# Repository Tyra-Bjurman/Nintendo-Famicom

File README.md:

# Nintendo Famicom
 Educational Nintendo Famicom Project

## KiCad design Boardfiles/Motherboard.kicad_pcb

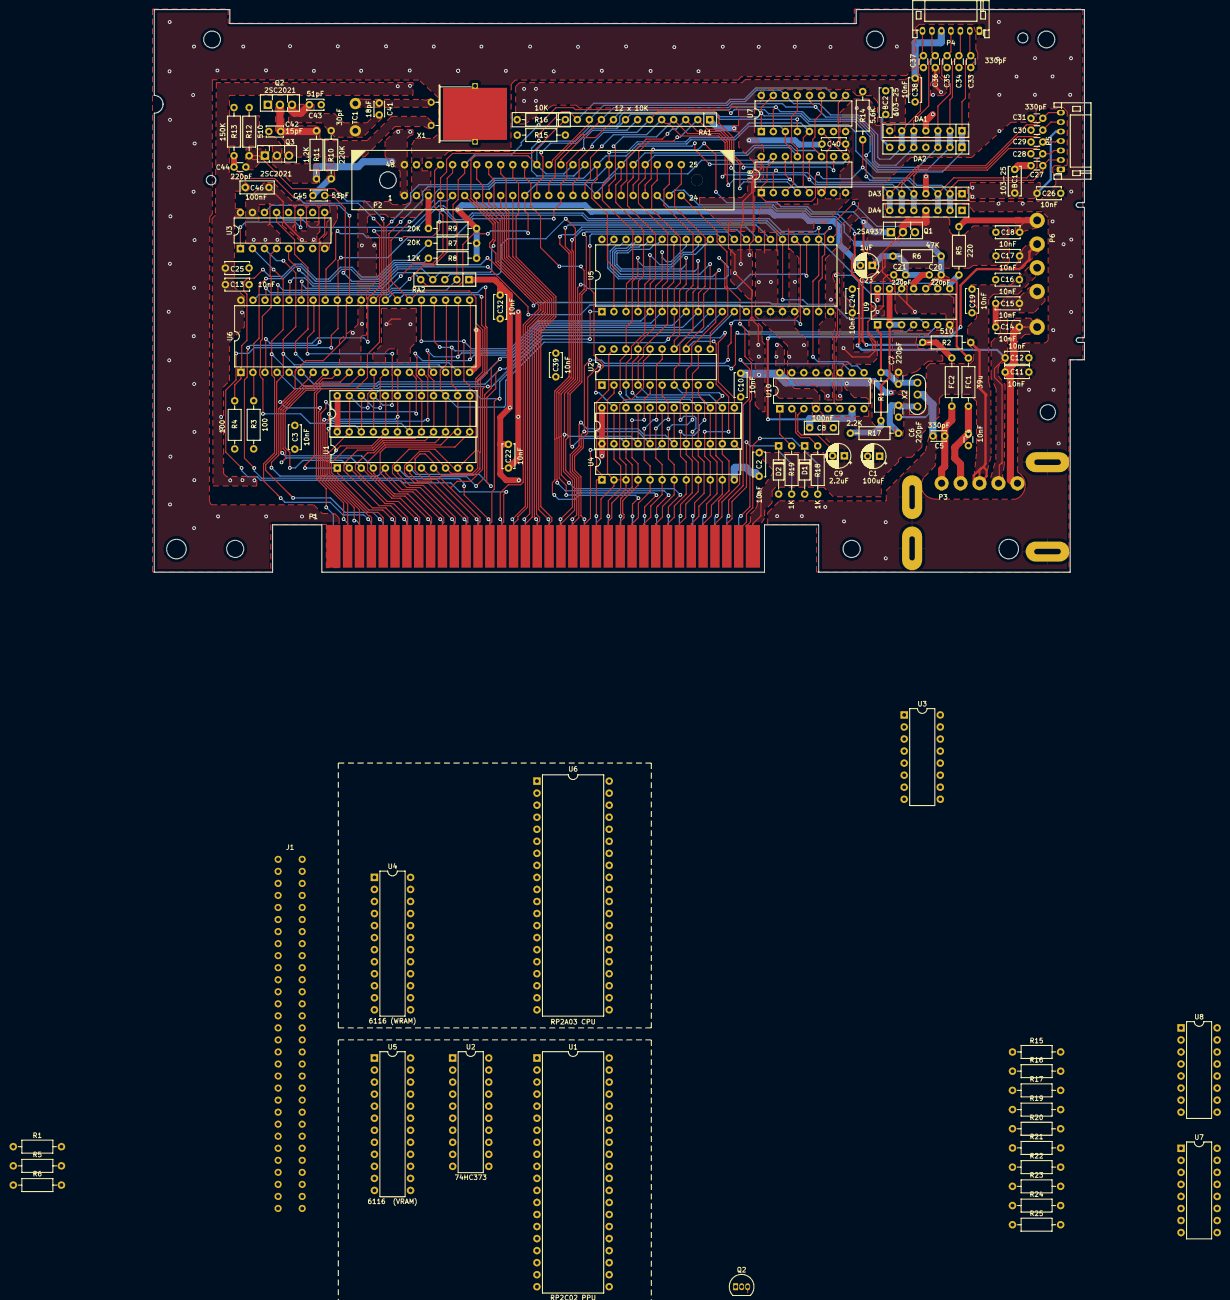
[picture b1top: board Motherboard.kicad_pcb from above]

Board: 2 copper layers, 196.3 x 118.7 mm, 124 parts (0 on the bottom side), 79 nets.

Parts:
 : DIP-24_W7.62mmSingleRow
 #2: DIP-24_W7.62mmSingleRow
BC1, BC2: 103-25; C_Disc_D6.0mm_W2.5mm_P5.00mm
C1: 100uF; CP_Radial_D5.0mm_P2.50mm
C2, C3, C10, C11, C12, C13, C14, C15, C16, C17, C18, C19, C22, C24, C26, C32, C38, C39, C40: 10nF; C_Disc_D5.0mm_W2.5mm_P5.00mm
C4: 10nF; C_Disc_D3.0mm_W1.6mm_P2.50mm
C5: 330pF; C_Disc_D3.0mm_W2.0mm_P2.50mm
C6, C7, C20, C21, C44: 220pF; C_Disc_D3.0mm_W1.6mm_P2.50mm
C8, C46: 100nF; C_Disc_D7.0mm_W2.5mm_P5.00mm
C9: 2.2uF; CP_Radial_D5.0mm_P2.50mm
C23: 1uF; CP_Radial_D5.0mm_P2.50mm
C25: (Unused); C_Disc_D5.0mm_W2.5mm_P5.00mm
C27, C28, C29, C30, C31, C33, C34, C35, C36, C37: 330pF; C_Disc_D3.0mm_W1.6mm_P2.50mm
C41: 18pF; C_Disc_D3.0mm_W2.0mm_P2.50mm
C42: 15pF; C_Disc_D3.4mm_W2.1mm_P2.50mm
C43, C45: 51pF; C_Disc_D3.4mm_W2.1mm_P2.50mm
D1, D2: ?; D_DO-35_SOD27_P10.16mm_Horizontal
DA1, DA3: DAN601; R_Array_SIP7
DA2, DA4: UPA64H; R_Array_SIP7
FC1: 39u; R_Axial_DIN0207_L6.3mm_D2.5mm_P10.16mm_Horizontal
FC2: Ferrite_Coil; R_Axial_DIN0207_L6.3mm_D2.5mm_P10.16mm_Horizontal
J1: Cart; 60 Pin connector
P1: 72-Pin Connector; NES_Edge_Connector
P2: EXP-Connector; EXP_Header
P3: MOD RF; Mod_RF
P4, P5: Controller Input; JST_PH_S7B-PH-K_1x07_P2.00mm_Horizontal
P6: PWR/RST IN; PowerReset-switch-In
Q1: 2SA937; TO-126-3_Vertical
Q2: KSA1015; TO-92_Inline
Q2#2, Q3: 2SC2021; TO-126-3_Vertical
R1, R5, R6, R15, R16, R17#2, R19#2, R20, R21, R22, R23, R24, R25: 10 kΩ; R_Axial_DIN0207_L6.3mm_D2.5mm_P10.16mm_Horizontal
R1#2: 1M; R_Axial_DIN0207_L6.3mm_D2.5mm_P10.16mm_Horizontal
R2, R12: 510; R_Axial_DIN0207_L6.3mm_D2.5mm_P10.16mm_Horizontal
R3, R4: 100; R_Axial_DIN0207_L6.3mm_D2.5mm_P10.16mm_Horizontal
R5#2: 220; R_Axial_DIN0207_L6.3mm_D2.5mm_P10.16mm_Horizontal
R6#2: 47K; R_Axial_DIN0207_L6.3mm_D2.5mm_P10.16mm_Horizontal
R7, R9: 20K; R_Axial_DIN0207_L6.3mm_D2.5mm_P10.16mm_Horizontal
R8: 12K; R_Axial_DIN0207_L6.3mm_D2.5mm_P10.16mm_Horizontal
R10: 220K; R_Axial_DIN0207_L6.3mm_D2.5mm_P10.16mm_Horizontal
R11: 1.2K; R_Axial_DIN0207_L6.3mm_D2.5mm_P10.16mm_Horizontal
R13: 150K; R_Axial_DIN0207_L6.3mm_D2.5mm_P10.16mm_Horizontal
R14: 5.6K; R_Axial_DIN0207_L6.3mm_D2.5mm_P10.16mm_Horizontal
R15#2: R15; R_Axial_DIN0207_L6.3mm_D2.5mm_P10.16mm_Horizontal
R16#2: 10K; R_Axial_DIN0207_L6.3mm_D2.5mm_P10.16mm_Horizontal_OverLappi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
R17: 2.2K; R_Axial_DIN0207_L6.3mm_D2.5mm_P10.16mm_Horizontal
R18, R19: 1K; R_Axial_DIN0207_L6.3mm_D2.5mm_P10.16mm_Horizontal
RA1: 12 x 10K; R_Array_SIP13
RA2: 4 x 6.8K; R_Array_SIP5
TC1: 30pF; TrimmerCap-THT
U1, U4: 6116 (WRAM); DIP-24_W7.62mm
U1#2, U5: RP2C02 PPU; DIP-40_W15.24mm
U2, U2#2: 74HC373; DIP-20_W7.62mm
U3, U3#2: 74HC139; DIP-16_W7.62mm
U4#2, U5#2: 6116 (VRAM); DIP-24_W7.62mm
U6: RP2A03 CPU; DIP-40_W15.24mm
U6#2: RP2A03 CPU
U7, U8: 74HC368; DIP-16_W7.62mm
U7#2: 40H368 (CI); DIP-16_W7.62mm
U8#2: 40H368 (CII); DIP-16_W7.62mm
U9: 74LS04; DIP-14_W7.62mm
U10: CIC; DIP-16_W7.62mm
X1: 21.477272 MHz; Crystal_HC49-U_Horizontal_1EP_style2
X2: 4MHz; Resonator_muRata_CSTLSxxxG-3Pin_W8.0mm_H3.0mm

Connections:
GND: J1.1 (GND), J1.16 (GND), Q2.2 (C), U1#2.17 (EXT3), U1#2.20 (GND), U2.1 (~OE), U2.10 (GND), U3#2.8 (GND), U3#2.15 (2E), U4.12 (GND), U4.20 (~OE), U5#2.12 (GND), U6#2.20 (GND), U6#2.30 (~RDY)
unnamed: R16.2, U7.1
unnamed: R17#2.2, U7.9 (1A4)
unnamed: R19#2.2, U7.6 (1A3)
unnamed: R20.2, U7.4 (1A2)
unnamed: R21.2, U8.1
unnamed: R22.2, U8.9 (1A4)
unnamed: R23.2, U8.6 (1A3)
unnamed: R24.2, U8.4 (1A2)
unnamed: R25.2, U6#2.39 (OUT_0)
unnamed: J1.13 (CPU_A00), U4.8 (A00)
unnamed: J1.12 (CPU_A01), U4.7 (A01)
unnamed: J1.11 (CPU_A02), U4.6 (A02)
unnamed: J1.10 (CPU_A03), U4.5 (A03)
unnamed: J1.9 (CPU_A04), U4.4 (A04)
unnamed: J1.8 (CPU_A05), U4.3 (A05)
unnamed: J1.7 (CPU_A06), U4.2 (A06)
unnamed: J1.6 (CPU_A07), U4.1 (A07)
unnamed: J1.5 (CPU_A08), U4.23 (A08)
unnamed: J1.4 (CPU_A09), U4.22 (A09)
unnamed: J1.3 (CPU_A10), U4.19 (A10)
unnamed: J1.2 (CPU_A11), U6#2.15 (A11)
unnamed: J1.33 (CPU_A12), U6#2.16 (A12)
unnamed: J1.34 (CPU_A13), U3#2.2
unnamed: J1.35 (CPU_A14), U3#2.3
unnamed: J1.43 (CPU_D00), U4.9 (D00)
unnamed: J1.42 (CPU_D01), U4.10 (D01)
unnamed: J1.41 (CPU_D02), U4.11 (D02)
unnamed: J1.40 (CPU_D03), U4.13 (D03)
unnamed: J1.39 (CPU_D04), U4.14 (D04)
unnamed: J1.38 (CPU_D05), U4.15 (D05)
unnamed: J1.37 (CPU_D06), U4.16 (D06)
unnamed: J1.36 (CPU_D07), U4.17 (D07)
unnamed: J1.14 (CPU_R/W), U4.21 (~WE)
unnamed: J1.32 (M2), U3#2.14
unnamed: J1.25 (PPU_A00), U2.2 (Q0)
unnamed: J1.24 (PPU_A01), U2.5 (Q1)
unnamed: J1.23 (PPU_A02), U2.6 (Q2)
unnamed: J1.22 (PPU_A03), U2.9 (Q3)
unnamed: J1.21 (PPU_A04), U2.12 (Q4)
unnamed: J1.20 (PPU_A05), U2.15 (Q5)
unnamed: J1.19 (PPU_A06), U2.16 (Q6)
unnamed: J1.50 (PPU_A07), U2.19 (Q7)
unnamed: J1.51 (PPU_A08), U1#2.30 (A08)
unnamed: J1.52 (PPU_A09), U1#2.29 (A09)
unnamed: J1.53 (PPU_A10), U1#2.28 (A10)
unnamed: J1.54 (PPU_A11), U1#2.27 (A11)
unnamed: J1.55 (PPU_A12), U1#2.26 (A12)
unnamed: J1.56 (PPU_A13), U1#2.25 (A13), U8.12 (2A1)
unnamed: J1.26 (PPU_D00), U2.3
unnamed: J1.27 (PPU_D01), U2.4
unnamed: J1.28 (PPU_D02), U2.7
unnamed: J1.29 (PPU_D03), U2.8
unnamed: J1.60 (PPU_D04), U2.13
unnamed: J1.59 (PPU_D05), U2.14
unnamed: J1.58 (PPU_D06), U2.17
unnamed: J1.57 (PPU_D07), U2.18
unnamed: J1.49 (PPU_~A13), U8.11 (~2Y1)
unnamed: J1.17 (PPU_~RD), U1#2.24 (~RD)
unnamed: J1.47 (PPU_~WR), U1#2.23 (~WR)
unnamed: J1.18 (VRAM_A10), U5#2.19 (A10)
unnamed: J1.48 (VRAM_~CE), U5#2.18 (~CS)
unnamed: J1.15 (~IRQ), U6#2.32 (~IRQ)
unnamed: J1.44 (~ROMSEL), U3#2.9 (2Y03)
unnamed: Q2.3 (B), U1#2.21 (VIDEO_OUT)
unnamed: U1#2.39 (ALE), U2.11 (LE)
unnamed: U1#2.18 (CLK), U6#2.29 (CLK)
unnamed: U1#2.13 (~CS), U3#2.5 (1Y01)
unnamed: U1#2.19 (~INT), U6#2.33 (~NMI)
unnamed: U3#2.1 (1E), U3#2.11 (2Y01)
unnamed: U3#2.4 (1Y00), U4.18 (~CS)
unnamed: U3#2.13 (2A01), U6#2.19 (A15)
unnamed: R15.2, U7.2 (1A1), U8.2 (1A1)
unnamed: U7.3 (~1Y1), U8.3 (~1Y1)
unnamed: U7.5 (~1Y2), U8.5 (~1Y2)
unnamed: U7.7 (~1Y3), U8.7 (~1Y3)
unnamed: U7.10 (~1Y4), U8.10 (~1Y4)
Reset: U1#2.22 (~RST), U6#2.3 (~RST)
VCC: J1.30 (VCC), J1.31 (VCC), R1.1, R5.1, R6.1, R15.1, R16.1, R17#2.1, R19#2.1, R20.1, R21.1, R22.1, R23.1, R24.1, R25.1, U1#2.40 (VCC), U2.20 (VCC), U3#2.16 (VCC), U4.24 (VCC), U5#2.24 (VCC), U6#2.40 (VCC)

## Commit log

2024-05-09 Moved files
2024-05-09 Create LICENSE
